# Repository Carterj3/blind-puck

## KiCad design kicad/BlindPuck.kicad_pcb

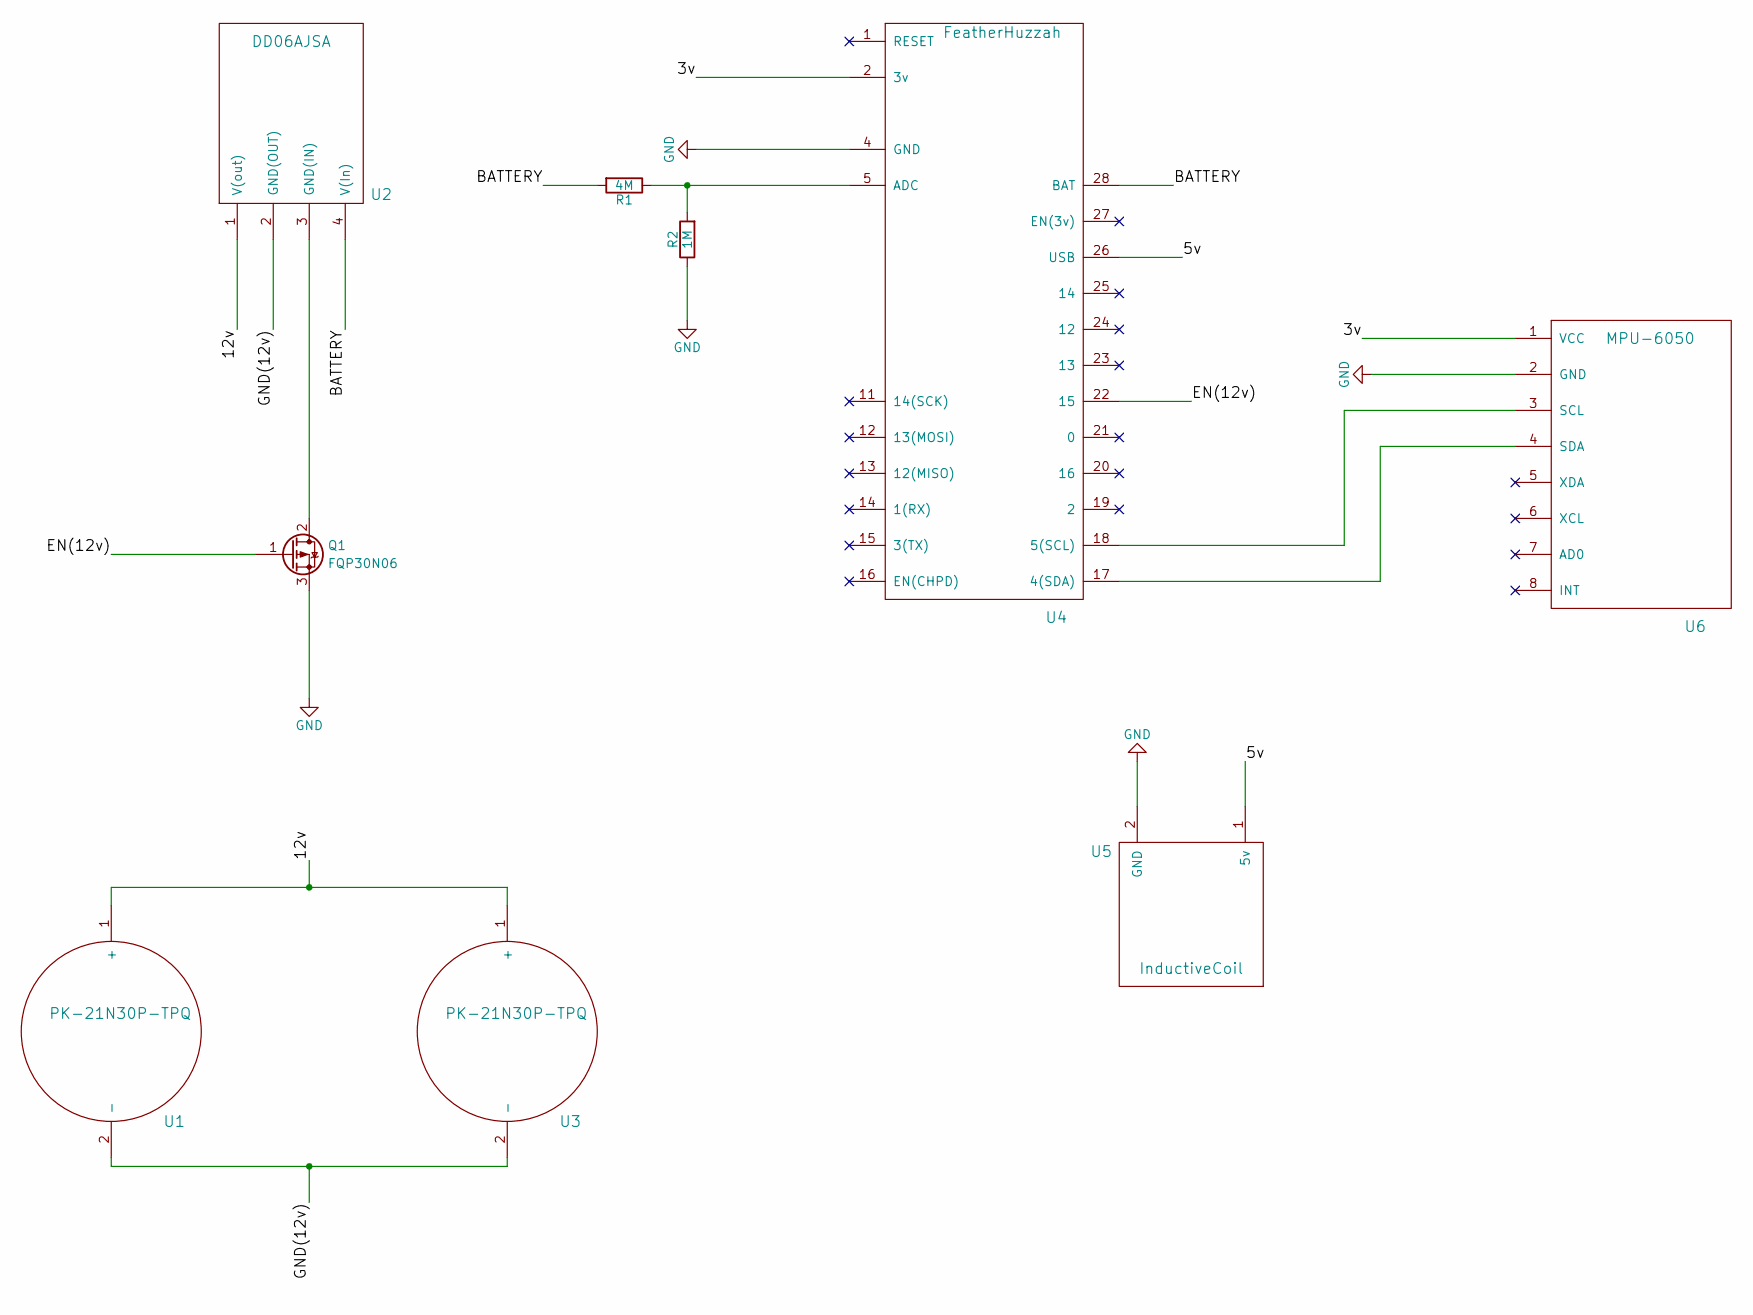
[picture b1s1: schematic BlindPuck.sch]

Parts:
Q1: FQP30N06; TO-220-3_Vertical
R1: 4M; R_Axial_DIN0207_L6.3mm_D2.5mm_P7.62mm_Horizontal
R2: 1M; R_Axial_DIN0207_L6.3mm_D2.5mm_P7.62mm_Horizontal
U1, U3: PK-21N30P-TPQ; 21N30P
U2: DD06AJSA
U4: FeatherHuzzah; Feather
U5: InductiveCoil; InductiveCoils(Rx)
U6: MPU-6050; MPU6050

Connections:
/3v: U4.2 (3v), U6.1 (VCC)
/5v: U4.26 (USB), U5.1 (5v)
/12v: U1.1 (+), U2.1 (V(out)), U3.1 (+)
/BATTERY: R1.2, U2.4 (V(In)), U4.28 (BAT)
/EN(12v): Q1.1 (G), U4.22 (15)
/GND(12v): U1.2 (-), U2.2 (GND(OUT)), U3.2 (-)
GND: Q1.3 (S), R2.1, U4.4 (GND), U5.2 (GND), U6.2 (GND)
unnamed: Q1.2 (D), U2.3 (GND(IN))
unnamed: R1.1, R2.2, U4.5 (ADC)
unnamed: U4.17 (4(SDA)), U6.4 (SDA)
unnamed: U4.18 (5(SCL)), U6.3 (SCL)

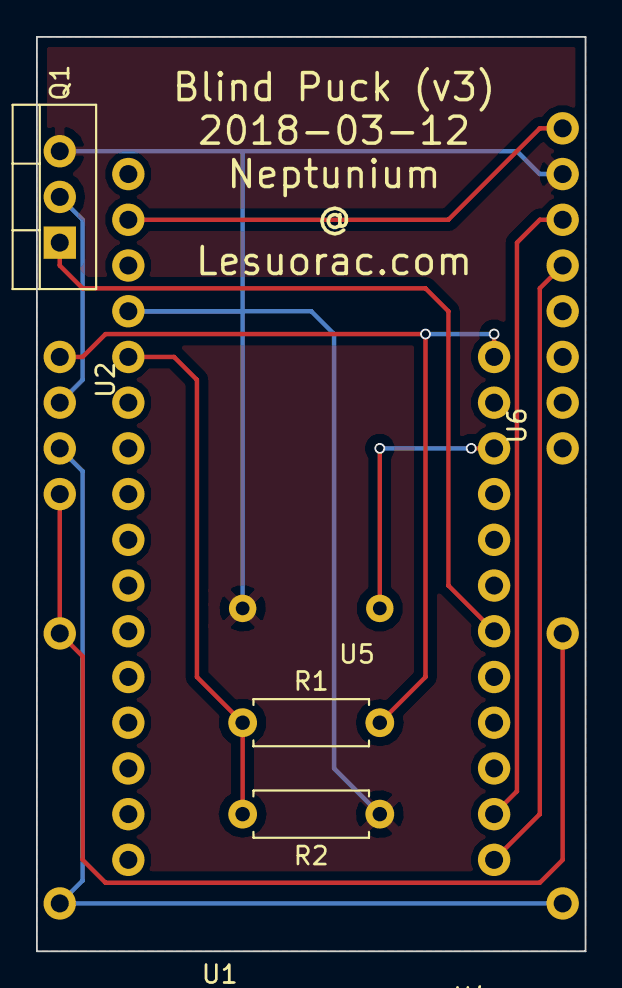
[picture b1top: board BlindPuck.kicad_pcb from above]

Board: 2 copper layers, 30.5 x 50.8 mm, 9 parts (0 on the bottom side), 11 nets.

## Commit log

2016-10-26 using default project
2016-10-27 updating to current test
2016-11-10 added endpoints to get data from devices
2016-11-10 added a tone vs DIO flag
2016-11-10 more experiementing
2016-11-10 added another drain
2016-11-14 adding helper files to avoid one large file changing webserver implementation back to original to get around blocking problem
2016-11-15 creating helper class
2016-11-16 reverting back to old wifi server as it wasn't blocking
2016-11-18 modified library to expose GRange commands updated internal library to assist with accel debugging
2016-11-18 fixed problem with i2c library. Accel recordings are now all in G's
2016-11-18 trying to prune filesize down
2016-11-19 added ability to read cfg from SPIFF will need to redo code layout though
2016-12-16 Updates due to switching to huzzah
2017-08-12 RISKY commit, added code to assist with speaker but issues with WiFi access point
2017-08-12 added accel functionality
2017-09-03 added charging
2017-09-04 added charging table
2017-09-04 fixed problem with timers, used bool instead of int
2017-09-08 added pdf documenting wiring
2018-03-11 modification to v3 for IMU
2018-03-13 fixed problems where the pcb's hole was too small
2018-03-13 removing libaries
2018-03-26 replacing the mpu6050
2018-03-31 fixing Bp v3 and adding new initial work on IMS board
